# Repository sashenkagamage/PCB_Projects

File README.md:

PCB projects I designed during my free time.

LED Torch

A simple circuit to turn on the LED by operating a button. 
The PCB Design: 

3D View:

Bread Board Power Supply

A circuit that provides power to the breadboard, which is deisgned to fit for the breadboard dimensions. 

The PCB Design:

3D View:

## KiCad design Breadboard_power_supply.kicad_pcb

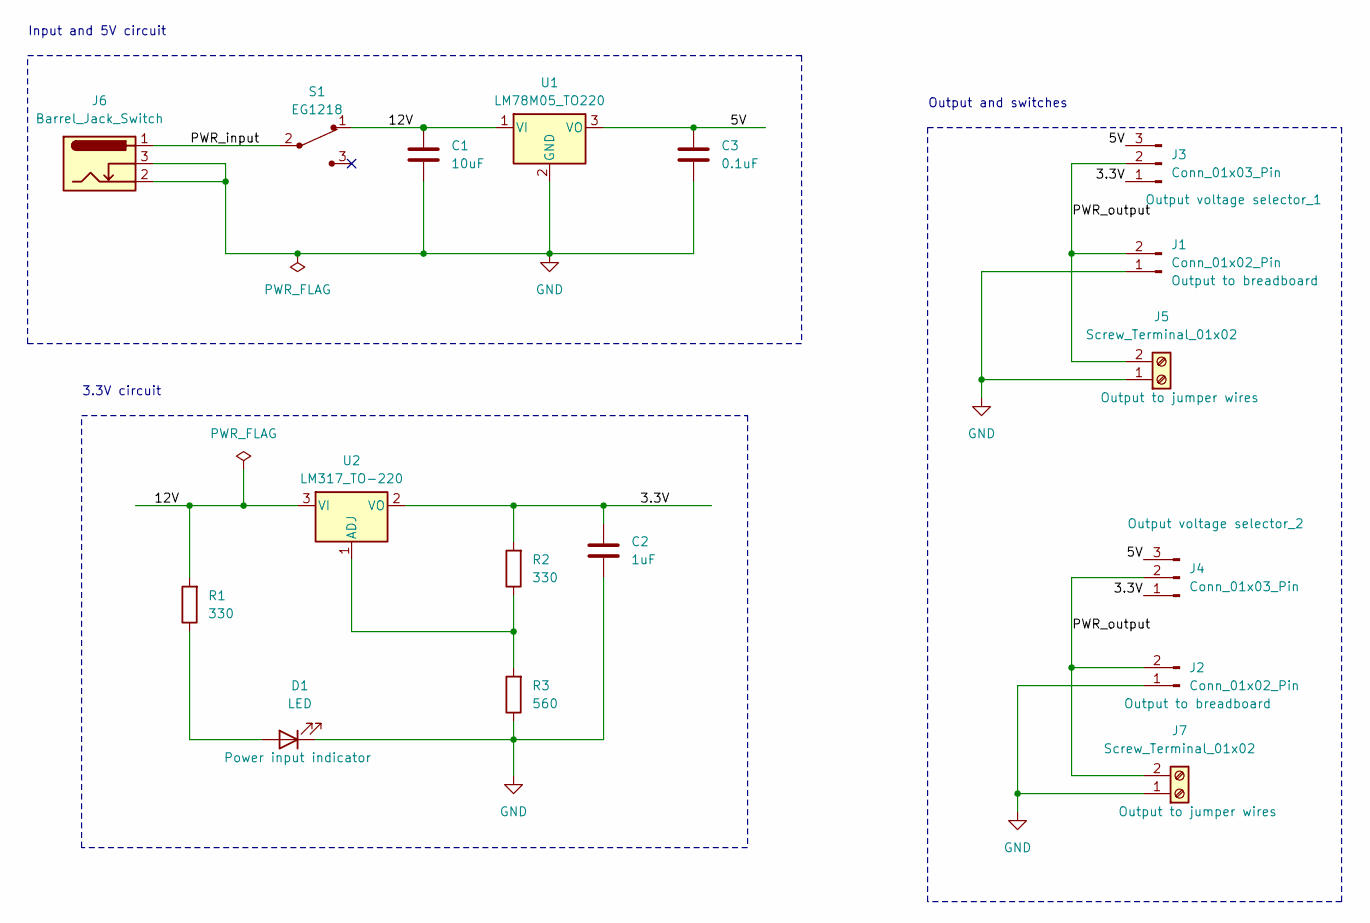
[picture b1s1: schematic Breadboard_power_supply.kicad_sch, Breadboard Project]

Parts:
C1: 10uF; C_Disc_D3.0mm_W1.6mm_P2.50mm
C2: 1uF; C_Disc_D3.0mm_W1.6mm_P2.50mm
C3: 0.1uF; C_Disc_D3.0mm_W1.6mm_P2.50mm
D1: LED; LED_D5.0mm
J1, J2: Conn_01x02_Pin; PinHeader_1x02_P2.54mm_Vertical
J3, J4: Conn_01x03_Pin; PinHeader_1x03_P2.54mm_Vertical
J5, J7: Screw_Terminal_01x02; TerminalBlock_bornier-2_P5.08mm
J6: Barrel_Jack_Switch; BarrelJack_Horizontal
R1, R2: 330; R_Axial_DIN0204_L3.6mm_D1.6mm_P7.62mm_Horizontal
R3: 560; R_Axial_DIN0204_L3.6mm_D1.6mm_P7.62mm_Horizontal
S1: EG1218; Switch_Slide_11.6x4mm_EG1218; MPN EG1218; Digi-Key_PN EG1903-ND
U1: LM78M05_TO220; TO-220-3_Vertical
U2: LM317_TO-220; TO-220-3_Vertical

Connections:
/3.3V: C2.1, J3.1, J4.1, R2.2, U2.2 (VO)
/5V: C3.1, J3.3, J4.3, U1.3 (VO)
/12V: C1.1, R1.2, S1.1, U1.1 (VI), U2.3 (VI)
/PWR_input: J6.1, S1.2
/PWR_output: J1.2, J2.2, J3.2, J4.2, J5.2, J7.2
GND: C1.2, C2.2, C3.2, D1.1 (K), J1.1, J2.1, J5.1, J6.2, J6.3, J7.1, R3.1, U1.2 (GND)
unnamed: D1.2 (A), R1.1
unnamed: R2.1, R3.2, U2.1 (ADJ)

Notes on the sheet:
Output and switches
Input and 5V circuit
3.3V circuit

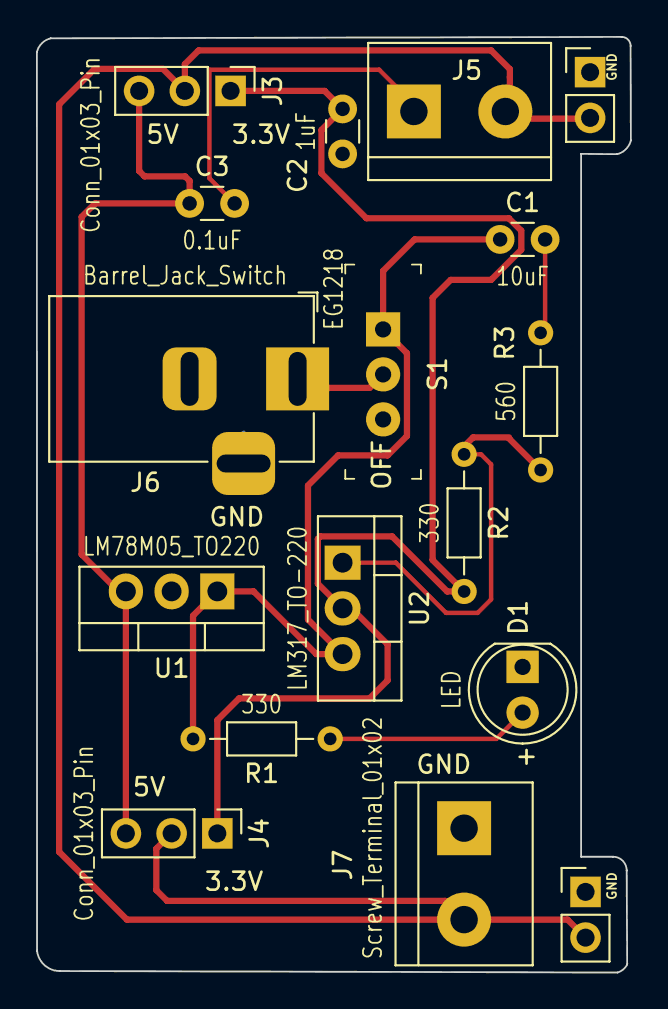
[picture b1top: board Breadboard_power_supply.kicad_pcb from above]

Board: 2 copper layers, 33.0 x 52.0 mm, 17 parts (0 on the bottom side), 8 nets.

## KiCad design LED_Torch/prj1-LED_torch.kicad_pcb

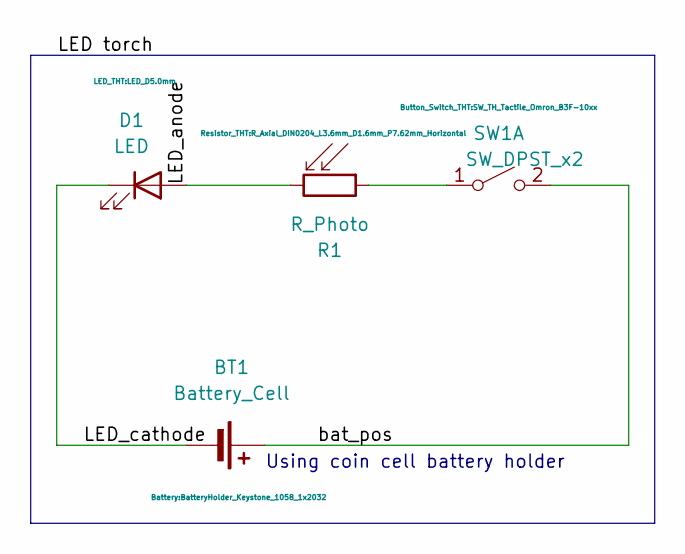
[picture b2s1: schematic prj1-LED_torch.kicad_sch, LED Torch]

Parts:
BT1: Battery_Cell; BatteryHolder_Keystone_1058_1x2032
D1: LED; LED_D5.0mm
R1: R_Photo; R_Axial_DIN0204_L3.6mm_D1.6mm_P7.62mm_Horizontal
SW1: SW_DPST_x2; SW_TH_Tactile_Omron_B3F-10xx

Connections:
/LED_anode: D1.2 (A), R1.2
/LED_cathode: BT1.2 (-), D1.1 (K)
/bat_pos: BT1.1 (+), SW1.2 (B)
unnamed: R1.1, SW1.1 (A)

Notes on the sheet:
Using coin cell battery holder

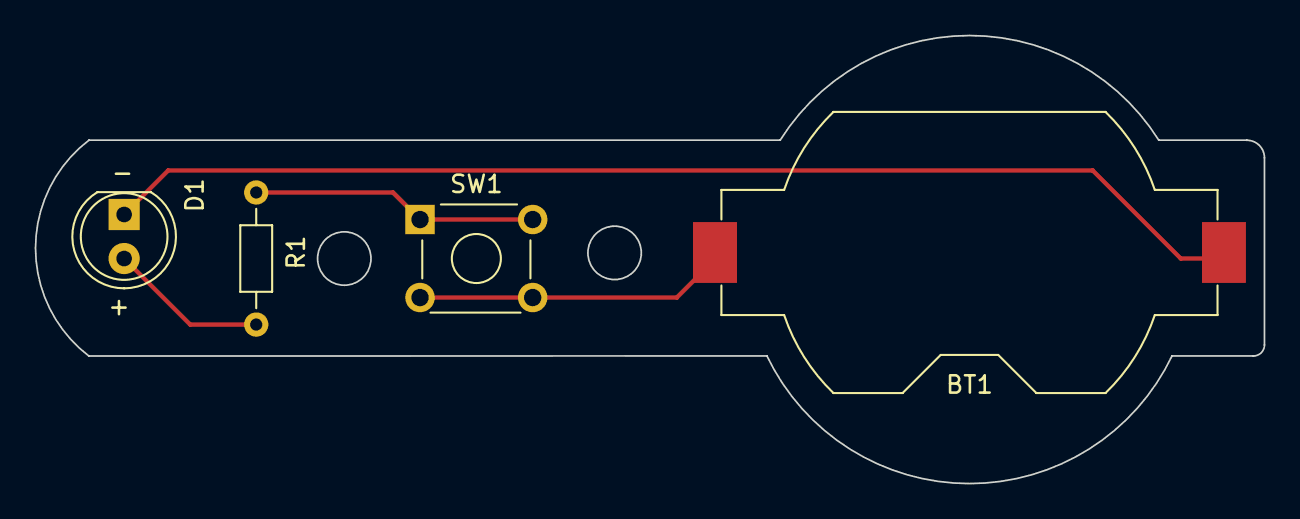
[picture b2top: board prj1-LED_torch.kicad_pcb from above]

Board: 2 copper layers, 70.9 x 25.8 mm, 4 parts (0 on the bottom side), 4 nets.

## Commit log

2024-08-02 Added LED torch
